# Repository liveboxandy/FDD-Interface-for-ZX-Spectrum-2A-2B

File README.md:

FDD interface for a ZX Spectrum 128 +2A/+2B or clone with +3e ROM's and a compatible expansion BUS.
There are files for both a horizontal PCB and a vertical PCB.

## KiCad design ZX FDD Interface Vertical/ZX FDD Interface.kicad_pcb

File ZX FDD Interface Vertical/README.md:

Floppy Disk Interface for ZX Spectrum +2A or any clone with +3e ROM's and compatible expansion BUS.
Based on information found on the web and various discussion groups.
This is a vertical PCB and allows for an extension PCB to be fitted so as to allow other adapters to be fitted to its rear (ZXHD and such).

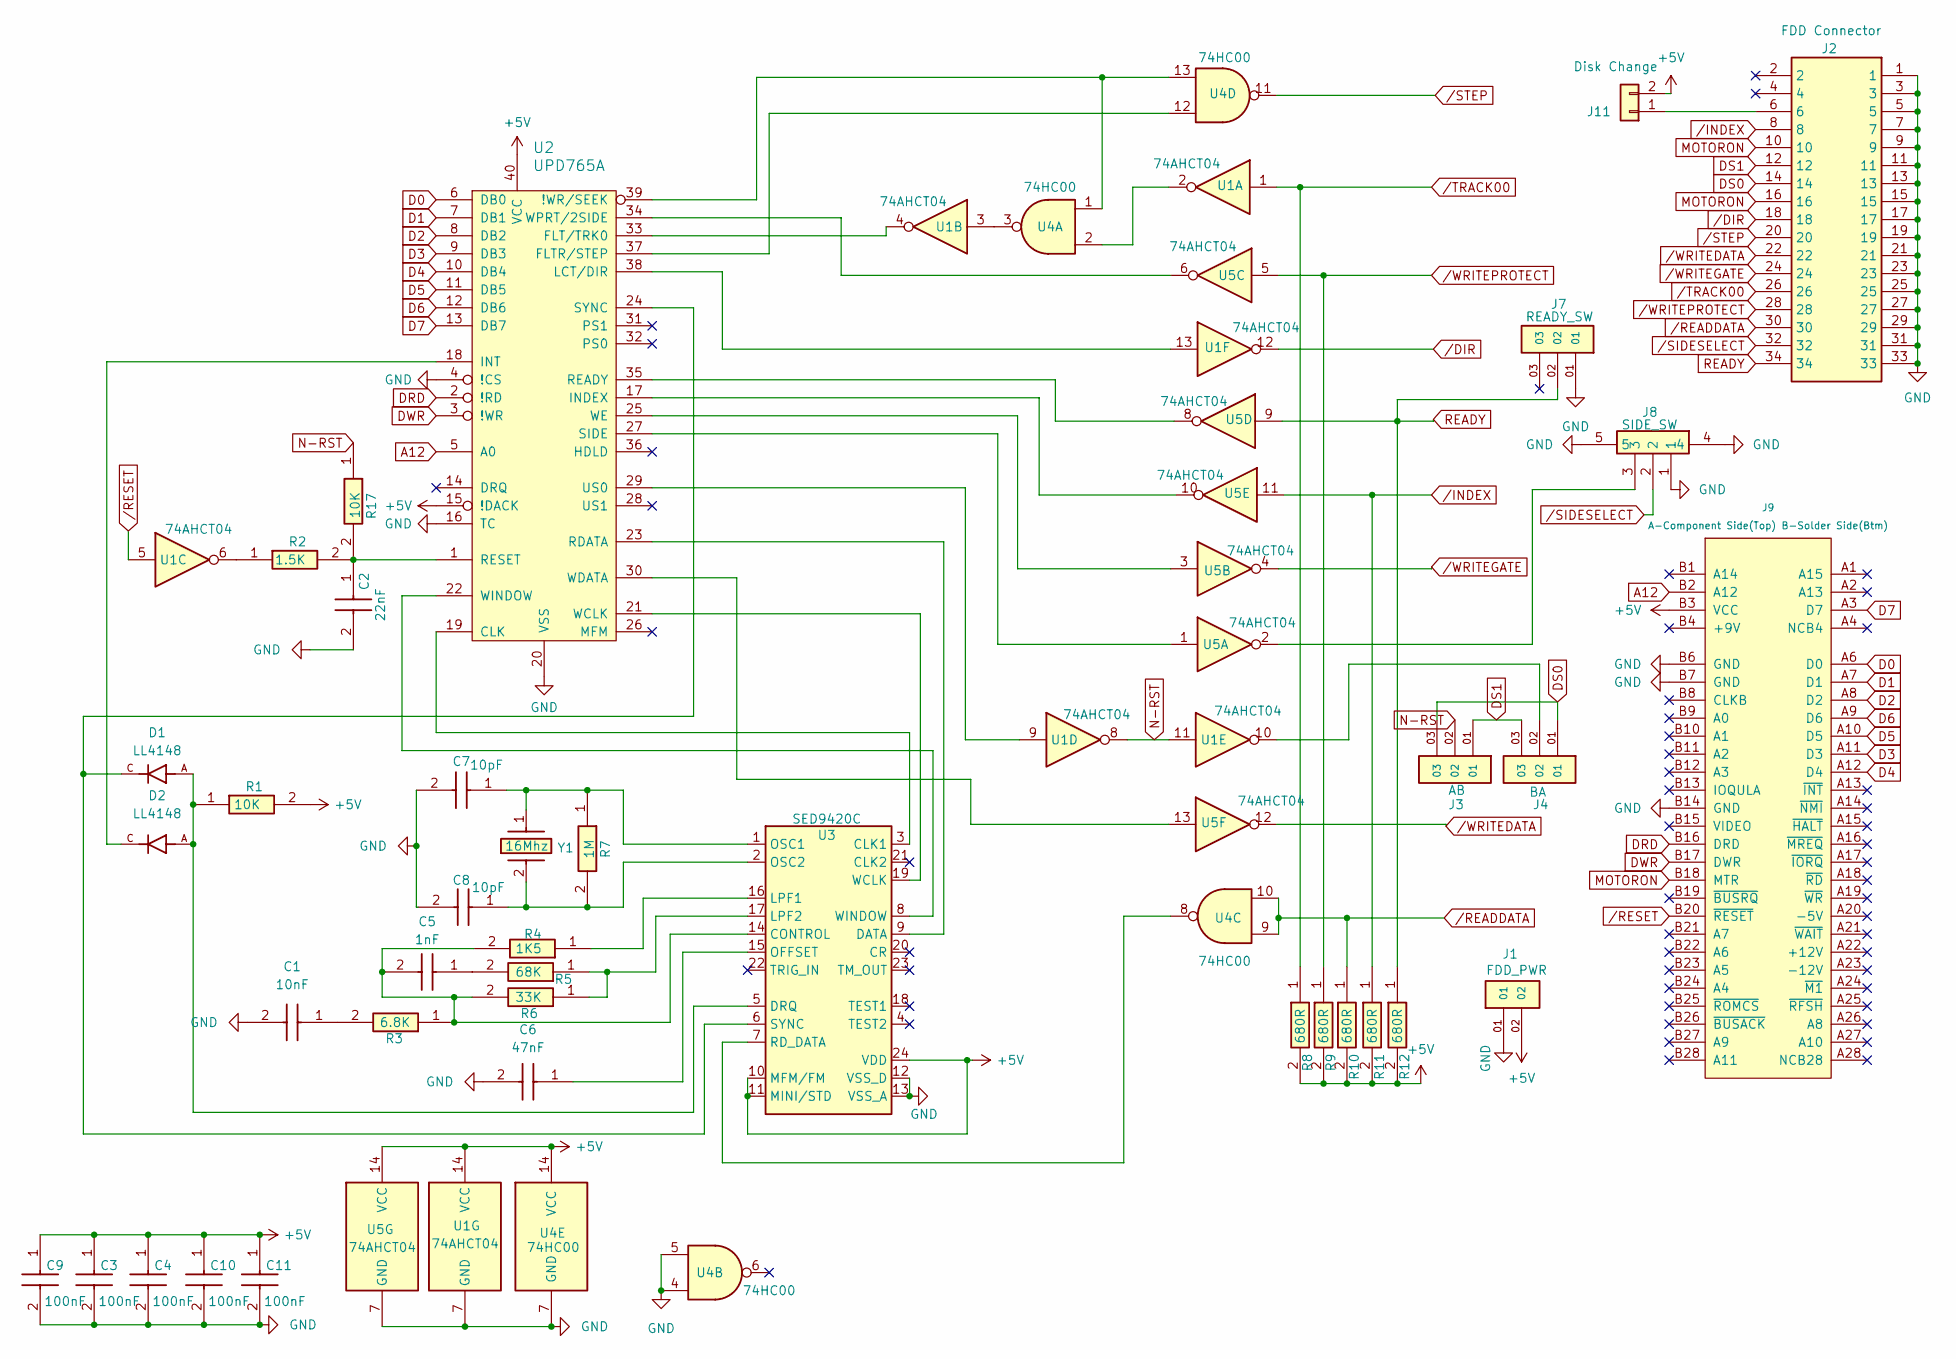
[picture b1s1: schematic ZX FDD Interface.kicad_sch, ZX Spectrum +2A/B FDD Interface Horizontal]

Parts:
C1: 10nF; Capacitor 0805; Mouser Part Number 80-C0805C104K4JAUTO
C2: 22nF; Capacitor 0805; Mouser Part Number 80-C0805C104K4JAUTO
C3, C4, C9, C10, C11: 100nF; Capacitor 0805; Mouser Part Number 80-C0805C104K4JAUTO
C5: 1nF; Capacitor 0805; Mouser Part Number 80-C0805C104K4JAUTO
C6: 47nF; Capacitor 0805; Mouser Part Number 80-C0805C104K4JAUTO
C7, C8: 10pF; Capacitor 0805; Mouser Part Number 80-C0805C104K4JAUTO
D1, D2: LL4148; Diode SMD LL4148; PARTREV 1.8
J1: FDD_PWR; TSW-102-07-G-S; PARTREV R
J2: FDD Connector; TSW-117-08-T-D-RA; Mouser Part Number 200-TSW11708TDRA
J3: AB; TSW-103-07-G-S; PARTREV R
J4: BA; TSW-103-07-G-S; PARTREV R
J7: READY_SW; TSW-103-07-G-S; PARTREV R
J8: SIDE_SW; Switch SPDT RA; Mouser Part Number 611-OS102011MA1QN1
J9: A-Component Side(Top) B-Solder Side(Btm); ZX_BUS_Vertical_B_Bottom_5.08mm
J11: Disk Change; PinHeader_1x02_P2.54mm_Vertical
R1, R17: 10K; Resistor 0805; Manufacturer_Part_Number 0805S8F1202P5E
R2: 1.5K; Resistor 0805; Manufacturer_Part_Number 0805S8F1202P5E
R3: 6.8K; Resistor 0805; Manufacturer_Part_Number 0805S8F1202P5E
R4: 1K5; Resistor 0805; Manufacturer_Part_Number 0805S8F1202P5E
R5: 68K; Resistor 0805; Manufacturer_Part_Number 0805S8F1202P5E
R6: 33K; Resistor 0805; Manufacturer_Part_Number 0805S8F1202P5E
R7: 1M; Resistor 0805; Manufacturer_Part_Number 0805S8F1202P5E
R8, R9, R10, R11, R12: 680R; Resistor 0805; Manufacturer_Part_Number 0805S8F1202P5E
U1, U5: 74AHCT04; SN74HCT04DR
U2: UPD765A
U3: SED9420C; SED9420
U4: 74HC00; SN74HCT00DR
Y1: 16Mhz; Crystal 16Mhz; Mouser Part Number 717-9B-16.000MBBK-B

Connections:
+5V: C3.1, C4.1, C9.1, C10.1, C11.1, J1.02, J9.B3 (VCC), J11.2, R1.2, R8.2, R9.2, R10.2, R11.2, R12.2, U1.14 (VCC), U2.15 (!DACK), U2.40 (VCC), U3.10 (MFM/FM), U3.11 (MINI/STD), U3.24 (VDD), U4.14 (VCC), U5.14 (VCC)
A12: J9.B2 (A12), U2.5 (A0)
D0: J9.A6 (D0), U2.6 (DB0)
D1: J9.A7 (D1), U2.7 (DB1)
D2: J9.A8 (D2), U2.8 (DB2)
D3: J9.A11 (D3), U2.9 (DB3)
D4: J9.A12 (D4), U2.10 (DB4)
D5: J9.A10 (D5), U2.11 (DB5)
D6: J9.A9 (D6), U2.12 (DB6)
D7: J9.A3 (D7), U2.13 (DB7)
DRD: J9.B16 (DRD), U2.2 (!RD)
DS0: J2.14, J3.03, J4.01
DS1: J2.12, J3.01, J4.03
DWR: J9.B17 (DWR), U2.3 (!WR)
GND: C1.2, C2.2, C3.2, C4.2, C6.2, C7.2, C8.2, C9.2, C10.2, C11.2, J1.01, J2.1, J2.3, J2.5, J2.7, J2.9, J2.11, J2.13, J2.15, J2.17, J2.19, J2.21, J2.23, J2.25, J2.27, J2.29, J2.31, J2.33, J7.01, J8.1, J8.4, J8.5, J9.B6 (GND), J9.B7 (GND), J9.B14 (GND), U1.7 (GND), U2.4 (!CS), U2.16 (TC), U2.20 (VSS), U3.12 (VSS_D), U3.13 (VSS_A), U4.4, U4.5, U4.7 (GND), U5.7 (GND)
MOTORON: J2.10, J2.16, J9.B18 (MTR)
N-RST: J3.02, R17.1, U1.8, U1.11
unnamed: C1.1, R3.2
unnamed: C5.1, R5.2
unnamed: J4.02, U1.10
unnamed: J8.3, U5.2
unnamed: J2.6, J11.1
unnamed: R2.1, U1.6
unnamed: U1.2, U4.2
unnamed: U1.3, U4.3
unnamed: U2.39 (!WR/SEEK), U4.1, U4.13
unnamed: U2.19 (CLK), U3.3 (CLK1)
unnamed: U2.37 (FLTR/STEP), U4.12
unnamed: U1.4, U2.33 (FLT/TRK0)
unnamed: U2.17 (INDEX), U5.10
unnamed: D2.C, U2.18 (INT)
unnamed: U1.13, U2.38 (LCT/DIR)
unnamed: U2.23 (RDATA), U3.9 (DATA)
unnamed: U2.35 (READY), U5.8
unnamed: C2.1, R2.2, R17.2, U2.1 (RESET)
unnamed: U2.27 (SIDE), U5.1
unnamed: D1.C, U2.24 (SYNC), U3.6 (SYNC)
unnamed: U1.9, U2.29 (US0)
unnamed: U2.21 (WCLK), U3.19 (WCLK)
unnamed: U2.30 (WDATA), U5.13
unnamed: U2.25 (WE), U5.3
unnamed: U2.22 (WINDOW), U3.8 (WINDOW)
unnamed: U2.34 (WPRT/2SIDE), U5.6
unnamed: C5.2, R3.1, R4.2, R6.2, U3.14 (CONTROL)
unnamed: D1.A, D2.A, R1.1, U3.5 (DRQ)
unnamed: R4.1, U3.16 (LPF1)
unnamed: R5.1, R6.1, U3.17 (LPF2)
unnamed: C6.1, U3.15 (OFFSET)
unnamed: C7.1, R7.1, U3.1 (OSC1), Y1.1
unnamed: C8.1, R7.2, U3.2 (OSC2), Y1.2 (CRYSTAL_2)
unnamed: U3.7 (RD_DATA), U4.8
READY: J2.34, J7.02, R12.1, U5.9
/DIR: J2.18, U1.12
/INDEX: J2.8, R11.1, U5.11
/READDATA: J2.30, R10.1, U4.9, U4.10
/RESET: J9.B20 (~RESET), U1.5
/SIDESELECT: J2.32, J8.2
/STEP: J2.20, U4.11
/TRACK00: J2.26, R8.1, U1.1
/WRITEDATA: J2.22, U5.12
/WRITEGATE: J2.24, U5.4
/WRITEPROTECT: J2.28, R9.1, U5.5

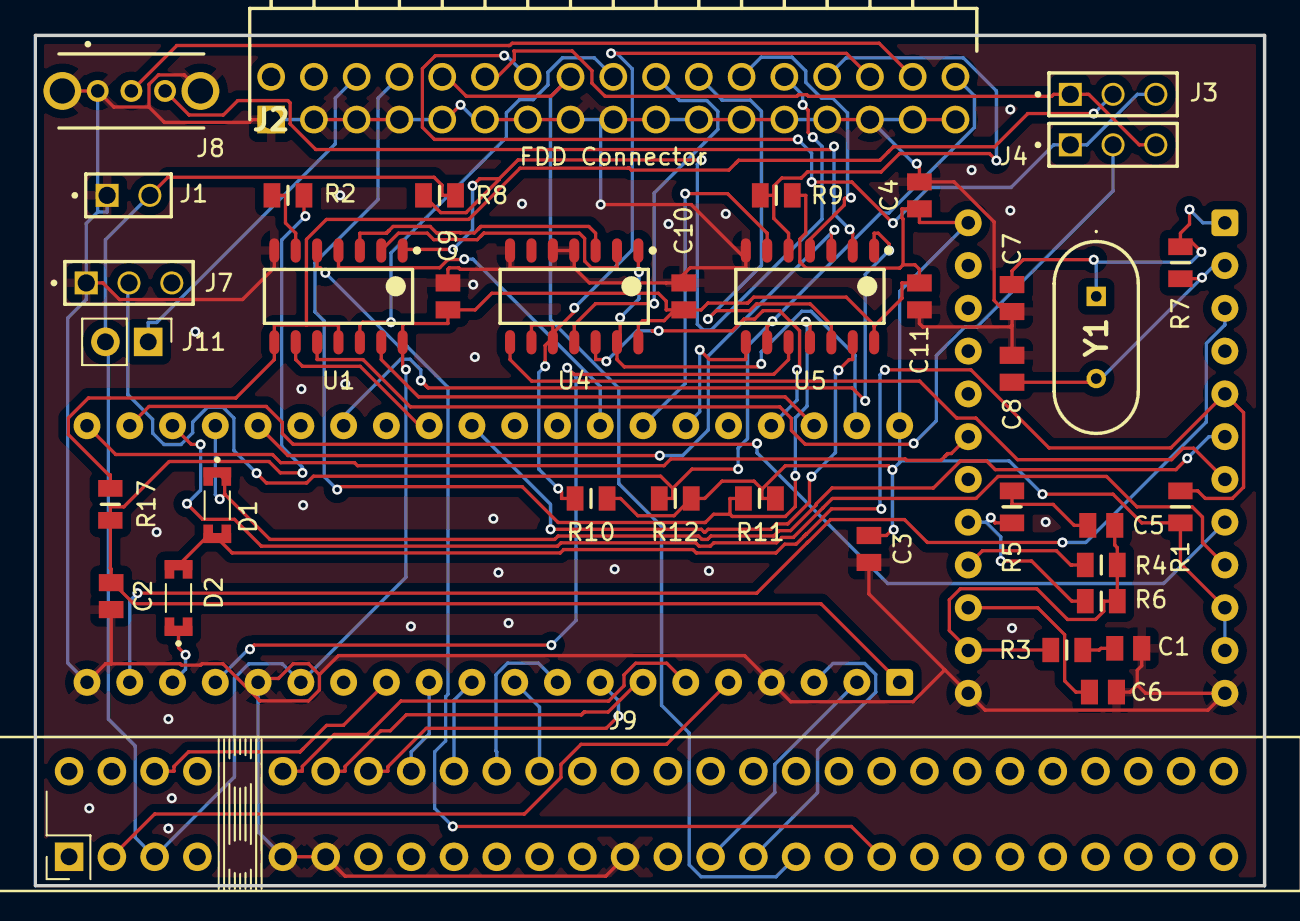
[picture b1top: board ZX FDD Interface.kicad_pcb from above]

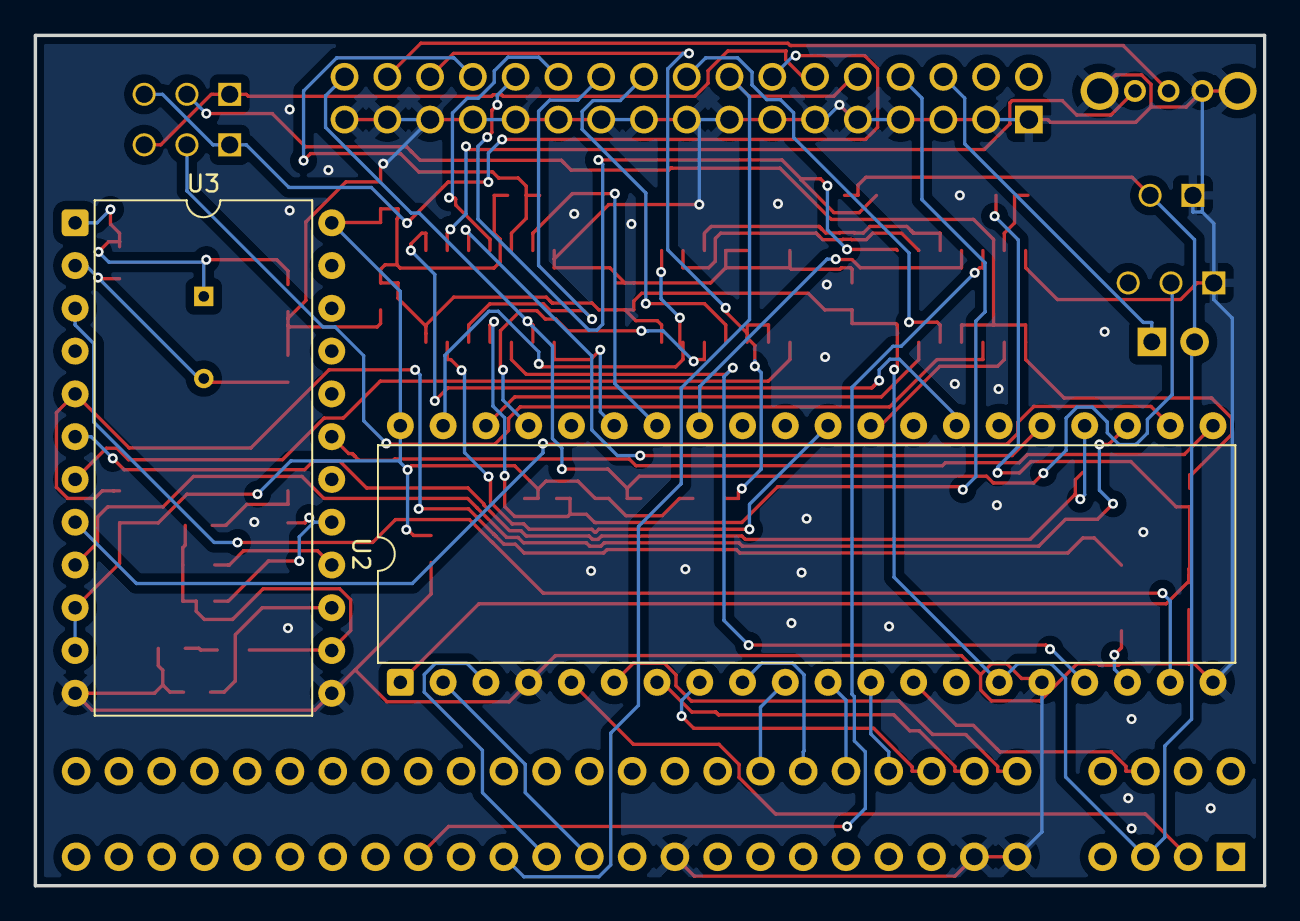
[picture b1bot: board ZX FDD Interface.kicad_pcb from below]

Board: 2 copper layers, 73.0 x 50.5 mm, 40 parts (2 on the bottom side), 62 nets.

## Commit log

2026-02-03 Add files via upload
    Initial upload of Horizontal PCB
2026-02-03 Add files via upload
    Initial release of the Vertical PCB files.
2026-02-03 Update README with FDD interface details
    Add description for FDD interface and PCB options.
